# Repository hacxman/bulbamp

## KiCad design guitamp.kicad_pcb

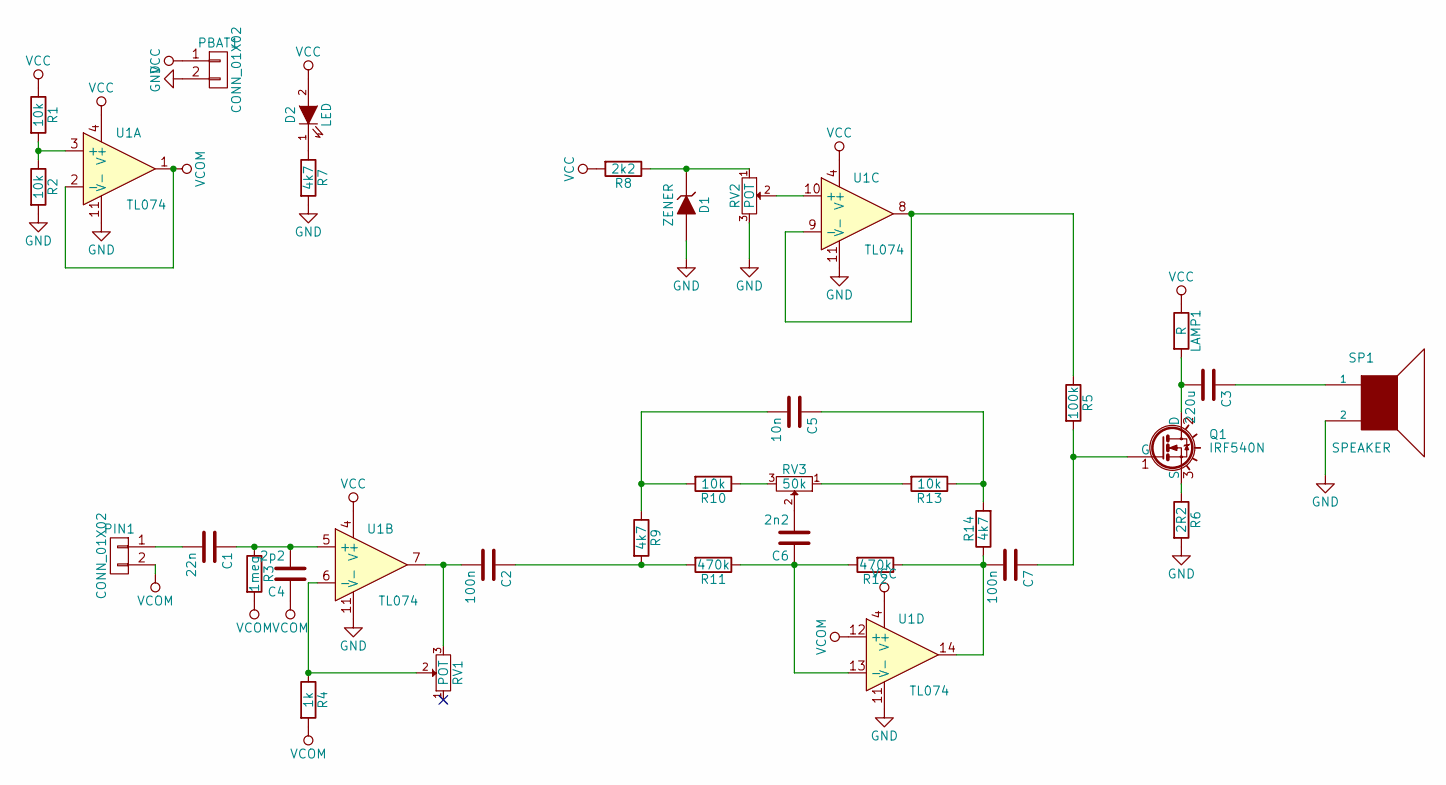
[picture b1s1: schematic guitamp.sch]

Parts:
C1: 22n; C_Disc_D7.5_P5
C2, C7: 100n; C_Disc_D7.5_P5
C3: 220u; C_Disc_D7.5_P5
C4: 2p2; C_Disc_D7.5_P5
C5: 10n; C_Disc_D7.5_P5
C6: 2n2; C_Disc_D7.5_P5
D1: ZENER; Diode_DO-41_SOD81_Horizontal_RM10
D2: LED; LED-5MM
LAMP1: R; Pin_Header_Straight_1x02
PBAT1: CONN_01X02; Pin_Header_Straight_1x02
PIN1: CONN_01X02; Pin_Header_Straight_1x02
Q1: IRF540N; TO-220_Neutral123_Vertical
R1, R2, R10, R13: 10k; Resistor_Horizontal_RM15mm
R3: 1meg; Resistor_Horizontal_RM15mm
R4: 1k; Resistor_Horizontal_RM15mm
R5: 100k; Resistor_Horizontal_RM15mm
R6: 2R2; Resistor_Horizontal_RM15mm
R7: 4k7; Resistor_Horizontal_RM7mm
R8: 2k2; Resistor_Horizontal_RM10mm
R9, R14: 4k7; Resistor_Horizontal_RM15mm
R11, R12: 470k; Resistor_Horizontal_RM15mm
RV1: POT; Pin_Header_Straight_1x03
RV2: POT; Potentiometer_Trimmer-Suntan-TSR-3386P
RV3: 50k; Pin_Header_Straight_1x03
SP1: SPEAKER; Pin_Header_Straight_1x02
U1: TL074; DIP-14_W7.62mm

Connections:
GND: D1.2 (A), PBAT1.2, R2.2, R6.2, R7.2, RV2.3, SP1.2, U1.11 (V-)
unnamed: C1.1, C4.2, R3.1, U1.5 (+)
unnamed: C1.2, PIN1.1
unnamed: C2.1, R9.2, R11.2
unnamed: C2.2, RV1.3, U1.7
unnamed: C3.1, SP1.1
unnamed: C3.2, LAMP1.2, Q1.2 (D)
unnamed: C5.1, R13.1, R14.2
unnamed: C5.2, R9.1, R10.2
unnamed: C6.1, R11.1, R12.2, U1.13 (-)
unnamed: C6.2, RV3.2
unnamed: C7.1, Q1.1 (G), R5.2
unnamed: C7.2, R12.1, R14.1, U1.14
unnamed: D1.1 (K), R8.1, RV2.1
unnamed: D2.1 (K), R7.1
unnamed: Q1.3 (S), R6.1
unnamed: R1.2, R2.1, U1.3 (+)
unnamed: R4.1, RV1.2, U1.6 (-)
unnamed: R5.1, U1.8, U1.9 (-)
unnamed: R10.1, RV3.3
unnamed: R13.2, RV3.1
unnamed: RV2.2, U1.10 (+)
VCC: D2.2 (A), LAMP1.1, PBAT1.1, R1.1, R8.2, U1.4 (V+)
VCOM: C4.1, PIN1.2, R3.2, R4.2, U1.1, U1.2 (-), U1.12 (+)

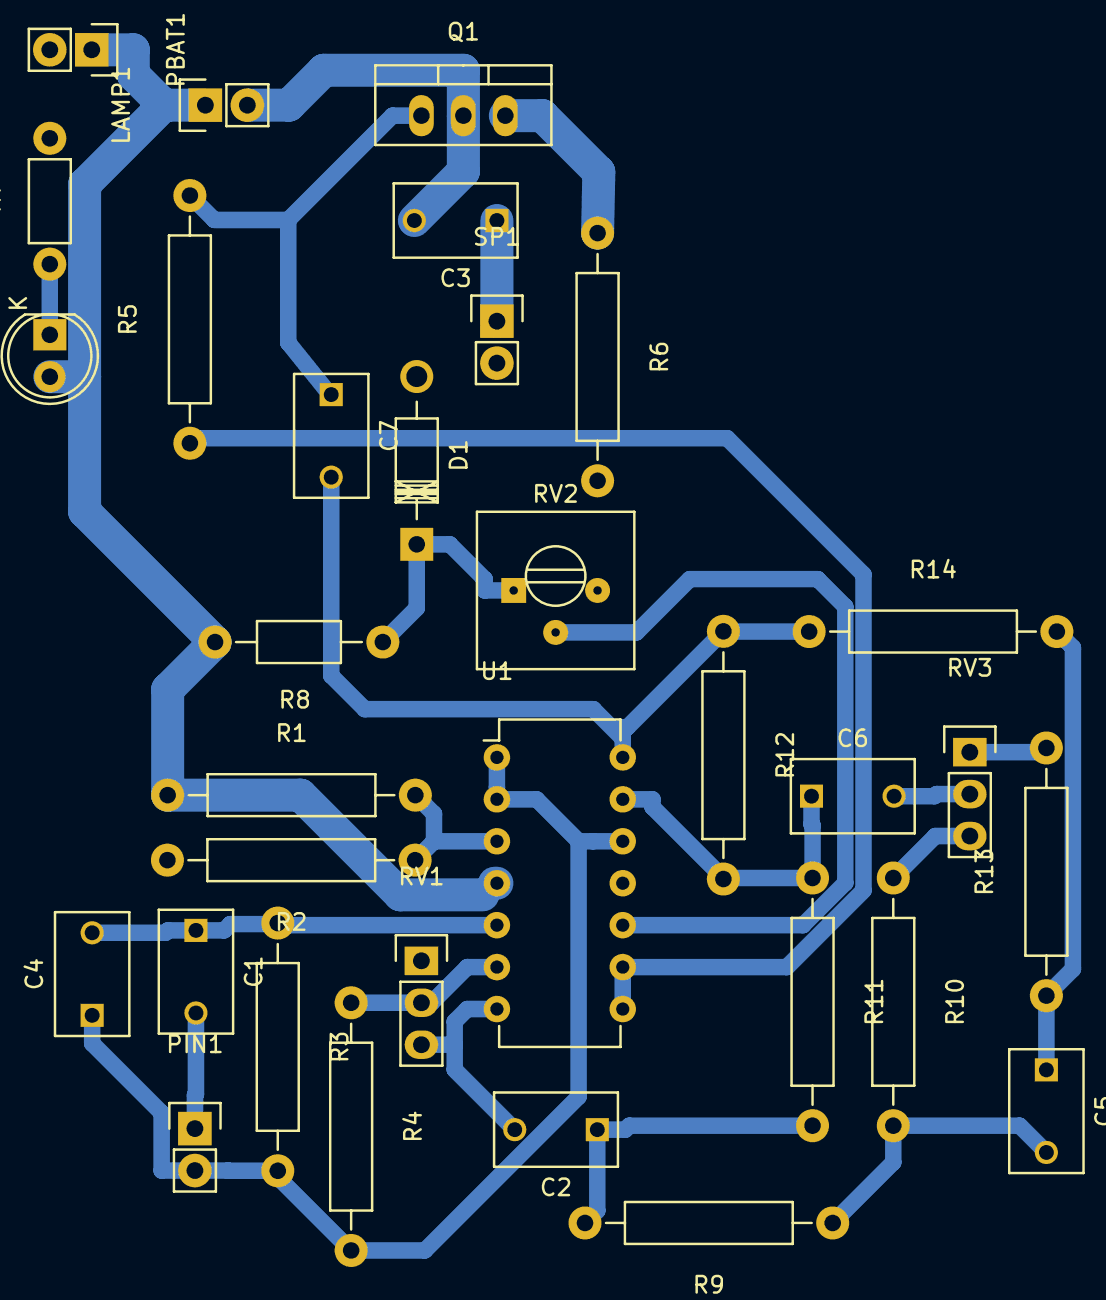
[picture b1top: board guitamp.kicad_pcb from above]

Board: 2 copper layers, 32 parts (0 on the bottom side), 24 nets.

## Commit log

2016-04-16 first
